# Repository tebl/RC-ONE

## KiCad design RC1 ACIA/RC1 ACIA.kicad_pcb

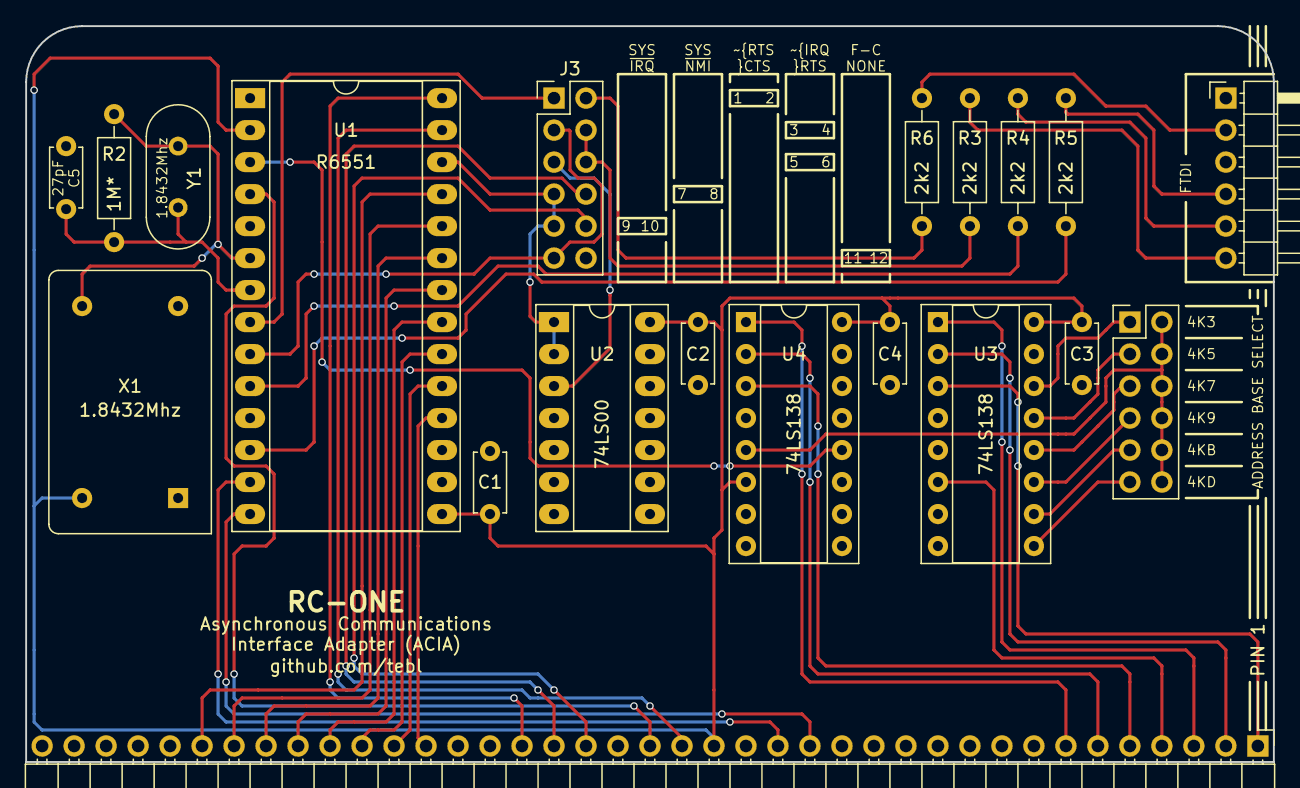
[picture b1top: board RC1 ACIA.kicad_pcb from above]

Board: 2 copper layers, 99.1 x 58.4 mm, 20 parts (0 on the bottom side), 46 nets.

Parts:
C1, C2, C3, C4: 100nF; C_Disc_D4.7mm_W2.5mm_P5.00mm
C5: 27pF; C_Disc_D4.7mm_W2.5mm_P5.00mm
J1: Expansion; Pin_Header_Angled_1x39_Pitch2.54mm
J2: ADDRESS; Pin_Header_Straight_2x06_Pitch2.54mm
J3: CONFIG; Pin_Header_Straight_2x06_Pitch2.54mm
J4: FTDI; Pin_Header_Angled_1x06_Pitch2.54mm
R2: 1M*; R_Axial_DIN0207_L6.3mm_D2.5mm_P10.16mm_Horizontal
R3, R4, R5, R6: 2k2; R_Axial_DIN0207_L6.3mm_D2.5mm_P10.16mm_Horizontal
U1: R6551; DIP-28_W15.24mm_Socket_LongPads
U2: 74LS00; DIP-14_W7.62mm_Socket_LongPads
U3, U4: 74LS138; DIP-16_W7.62mm_Socket
X1: 1.8432Mhz; Oscillator_DIP-14
Y1: 1.8432Mhz; Crystal_HC49-4H_Vertical

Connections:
/4K3: J2.1, U3.14
/4K5: J2.3, U3.13
/4K7: J2.5, U3.12
/4K9: J2.7, U3.11
/4KB: J2.9, U3.10
/4KD: J2.11, U3.9
/A0: J1.16, U1.13
/A1: J1.15, U1.14
/A9: J1.7, U4.1
/A10: J1.6, U4.2
/A11: J1.5, U4.3
/A12: J1.4, U3.6
/A13: J1.3, U3.1
/A14: J1.2, U3.2
/A15: J1.1, U3.3
/D0: J1.27, U1.18
/D1: J1.28, U1.19
/D2: J1.29, U1.20
/D3: J1.30, U1.21
/D4: J1.31, U1.22
/D5: J1.32, U1.23
/D6: J1.33, U1.24
/D7: J1.34, U1.25
/PHI2: J1.19, U1.27
/R/~W: J1.24, U1.28
/RxD: R5.1, U1.12
/TxD: R4.1, U1.10
/~IRQ: J1.22, J3.10
/~NMI: J1.23, J3.8
/~RESET: J1.20, U1.4
GND: C1.2, C2.2, C3.2, C4.2, C5.1, J1.17, J3.12, J4.1, U1.1, U1.16, U1.17, U2.4, U2.5, U2.7, U2.9, U2.10, U2.12, U2.13, U3.4, U3.5, U3.8, U4.4, U4.8, X1.7
unnamed: C5.2, R2.2, U1.7, Y1.2
unnamed: J2.2, J2.4, J2.6, J2.8, J2.10, J2.12, U4.5
unnamed: J3.1, U1.8
unnamed: J3.2, R6.1
unnamed: J3.4, J3.6, R3.1
unnamed: J3.5, U2.3
unnamed: J3.7, J3.9, U1.26, U2.1, U2.2
unnamed: J3.3, J3.11, U1.9
unnamed: J4.2, R6.2
unnamed: J4.4, R5.2
unnamed: J4.5, R4.2
unnamed: J4.6, R3.2
unnamed: R2.1, U1.6, X1.8, Y1.1
VCC: C1.1, C2.1, C3.1, C4.1, J1.18, U1.2, U1.15, U2.14, U3.16, U4.6, U4.16, X1.14
~CS_ACIA: U1.3, U4.12

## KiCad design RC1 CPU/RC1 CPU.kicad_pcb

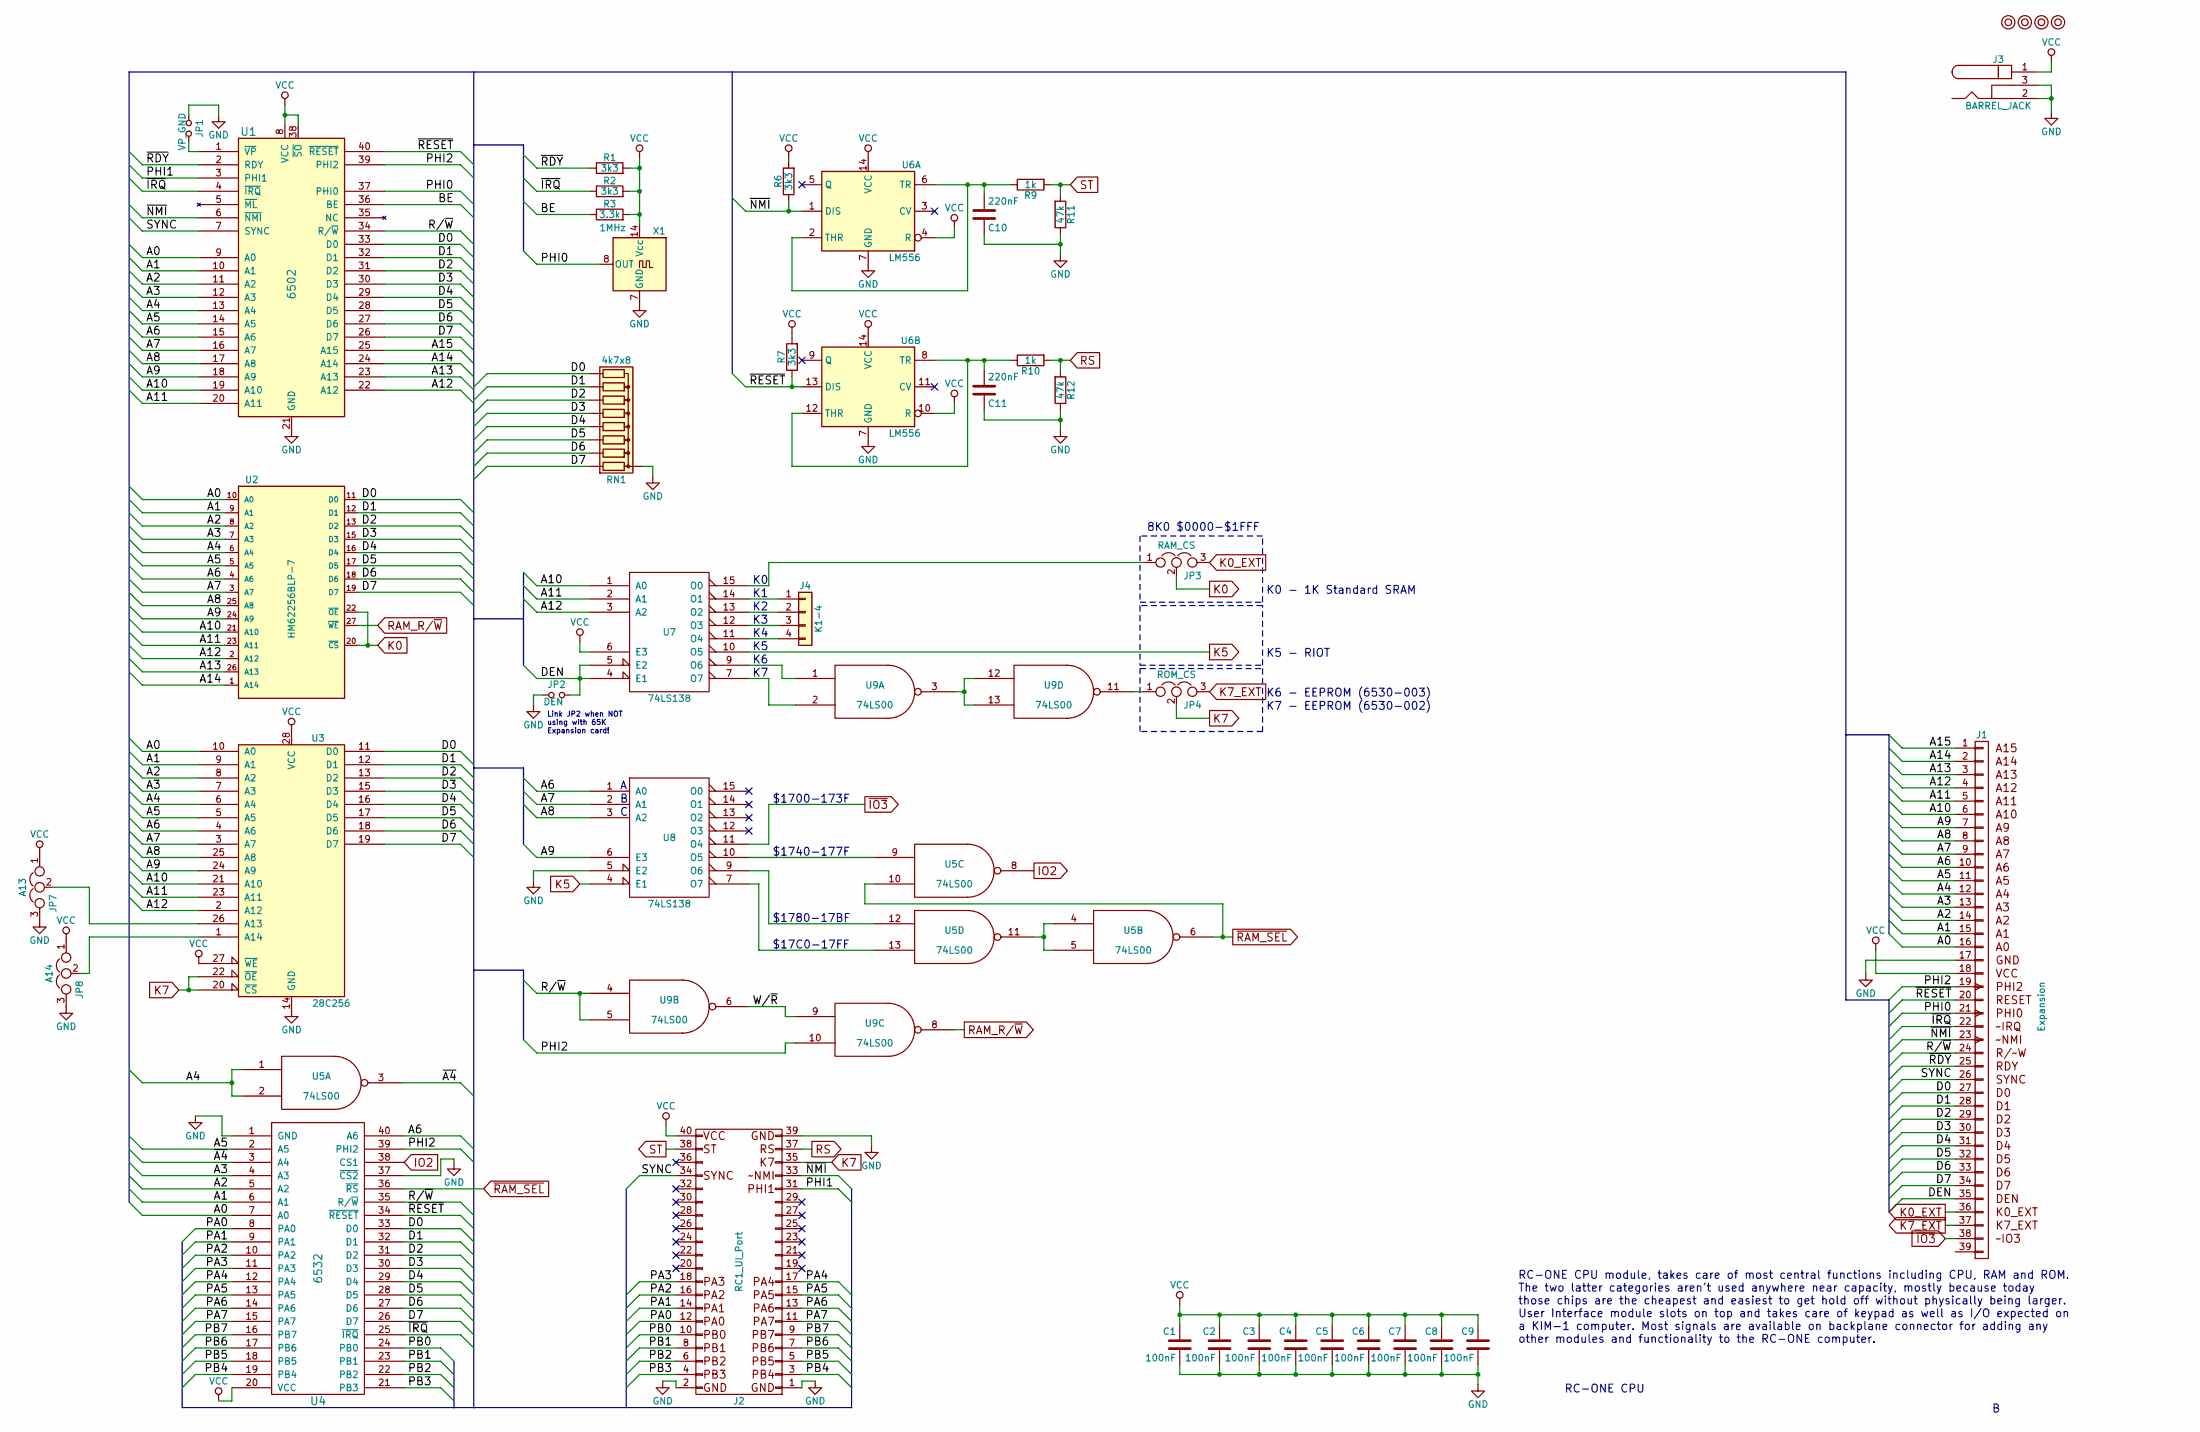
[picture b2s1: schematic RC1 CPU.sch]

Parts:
C1, C2, C3, C4, C5, C6, C7, C8, C9: 100nF; C_Disc_D4.7mm_W2.5mm_P5.00mm
C10, C11: 220nF; C_Disc_D4.7mm_W2.5mm_P5.00mm
J1: Expansion; Pin_Header_Angled_1x39_Pitch2.54mm
J2: RC1_UI_Port; Pin_Header_Straight_2x20_Pitch2.54mm
J3: BARREL_JACK
J4: K1-4; Pin_Header_Straight_1x04_Pitch2.54mm
JP1: VP_GND; Pin_Header_Straight_1x02_Pitch2.54mm
JP2: DEN; Pin_Header_Straight_1x02_Pitch2.54mm
JP3: RAM_CS; Pin_Header_Straight_1x03_Pitch2.54mm
JP4: ROM_CS; Pin_Header_Straight_1x03_Pitch2.54mm
JP7: A13; Pin_Header_Straight_1x03_Pitch2.54mm
JP8: A14; Pin_Header_Straight_1x03_Pitch2.54mm
M1, M2, M3, M4: Mounting; 1pin
R1, R2, R6, R7: 3k3; R_Axial_DIN0207_L6.3mm_D2.5mm_P10.16mm_Horizontal
R3: 3.3k; R_Axial_DIN0207_L6.3mm_D2.5mm_P10.16mm_Horizontal
R9, R10: 1k; R_Axial_DIN0207_L6.3mm_D2.5mm_P10.16mm_Horizontal
R11, R12: 47k; R_Axial_DIN0207_L6.3mm_D2.5mm_P10.16mm_Horizontal
RN1: 4k7x8; R_Array_SIP9
U1: 6502; DIP-40_W15.24mm_Socket
U2: HM62256BLP-7; DIP-28_W15.24mm_Socket
U3: 28C256; DIP-28_W15.24mm_Socket
U4: 6532; DIP-40_W15.24mm_Socket
U5, U9: 74LS00; DIP-14_W7.62mm_Socket
U6: LM556; DIP-14_W7.62mm_Socket
U7, U8: 74LS138; DIP-16_W7.62mm_Socket
X1: 1MHz; Oscillator_DIP-14

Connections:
/A0: J1.16 (A0), U1.9 (A0), U2.10 (A0), U3.10 (A0), U4.7 (A0)
/A1: J1.15 (A1), U1.10 (A1), U2.9 (A1), U3.9 (A1), U4.6 (A1)
/A2: J1.14 (A2), U1.11 (A2), U2.8 (A2), U3.8 (A2), U4.5 (A2)
/A3: J1.13 (A3), U1.12 (A3), U2.7 (A3), U3.7 (A3), U4.4 (A3)
/A4: J1.12 (A4), U1.13 (A4), U2.6 (A4), U3.6 (A4), U5.1, U5.2
/A5: J1.11 (A5), U1.14 (A5), U2.5 (A5), U3.5 (A5), U4.2 (A5)
/A6: J1.10 (A6), U1.15 (A6), U2.4 (A6), U3.4 (A6), U4.40 (A6), U8.1 (A0)
/A7: J1.9 (A7), U1.16 (A7), U2.3 (A7), U3.3 (A7), U8.2 (A1)
/A8: J1.8 (A8), U1.17 (A8), U2.25 (A8), U3.25 (A8), U8.3 (A2)
/A9: J1.7 (A9), U1.18 (A9), U2.24 (A9), U3.24 (A9), U8.6 (E3)
/A10: J1.6 (A10), U1.19 (A10), U2.21 (A10), U3.21 (A10), U7.1 (A0)
/A11: J1.5 (A11), U1.20 (A11), U2.23 (A11), U3.23 (A11), U7.2 (A1)
/A12: J1.4 (A12), U1.22 (A12), U2.2 (A12), U3.2 (A12), U7.3 (A2)
/A13: J1.3 (A13), U1.23 (A13), U2.26 (A13)
/A14: J1.2 (A14), U1.24 (A14), U2.1 (A14)
/A15: J1.1 (A15), U1.25 (A15)
/BE: R3.1, U1.36 (BE)
/D0: J1.27 (D0), RN1.9 (R8), U1.33 (D0), U2.11 (D0), U3.11 (D0), U4.33 (D0)
/D1: J1.28 (D1), RN1.8 (R7), U1.32 (D1), U2.12 (D1), U3.12 (D1), U4.32 (D1)
/D2: J1.29 (D2), RN1.7 (R6), U1.31 (D2), U2.13 (D2), U3.13 (D2), U4.31 (D2)
/D3: J1.30 (D3), RN1.6 (R5), U1.30 (D3), U2.15 (D3), U3.15 (D3), U4.30 (D3)
/D4: J1.31 (D4), RN1.5 (R4), U1.29 (D4), U2.16 (D4), U3.16 (D4), U4.29 (D4)
/D5: J1.32 (D5), RN1.4 (R3), U1.28 (D5), U2.17 (D5), U3.17 (D5), U4.28 (D5)
/D6: J1.33 (D6), RN1.3 (R2), U1.27 (D6), U2.18 (D6), U3.18 (D6), U4.27 (D6)
/D7: J1.34 (D7), RN1.2 (R1), U1.26 (D7), U2.19 (D7), U3.19 (D7), U4.26 (D7)
/DEN: J1.35 (TX), JP2.2, U7.4 (E1), U7.5 (E2)
/PA0: J2.12, U4.8 (PA0)
/PA1: J2.14, U4.9 (PA1)
/PA2: J2.16, U4.10 (PA2)
/PA3: J2.18, U4.11 (PA3)
/PA4: J2.17, U4.12 (PA4)
/PA5: J2.15, U4.13 (PA5)
/PA6: J2.13, U4.14 (PA6)
/PA7: J2.11, U4.15 (PA7)
/PB0: J2.10, U4.24 (PB0)
/PB1: J2.8, U4.23 (PB1)
/PB2: J2.6, U4.22 (PB2)
/PB3: J2.4, U4.21 (PB3)
/PB4: J2.3, U4.19 (PB4)
/PB5: J2.5, U4.18 (PB5)
/PB6: J2.7, U4.17 (PB6)
/PB7: J2.9, U4.16 (PB7)
/PHI0: J1.21 (PHI0), U1.37 (PHI0), X1.8 (OUT)
/PHI1: J2.31, U1.3 (PHI1)
/PHI2: J1.19 (PHI2), U1.39 (PHI2), U4.39 (PHI2), U9.10
/R/~W: J1.24 (RW), U1.34 (R/~W), U4.35 (R/~W), U9.4, U9.5
/SYNC: J1.26 (SYNC), J2.34, U1.7 (SYNC)
/W/~R: U9.6, U9.9
/~A4: U4.3 (A4), U5.3
/~IRQ: J1.22 (IRQ), R2.1, U1.4 (~IRQ), U4.25 (~IRQ)
/~NMI: J1.23 (PHI1), J2.33, R6.1, U1.6 (~NMI), U6.1 (DIS)
/~RDY: J1.25 (READY), R1.1, U1.2 (RDY)
/~RESET: J1.20 (RESET), R7.1, U1.40 (~RESET), U4.34 (~RESET), U6.13 (DIS)
GND: C1.2, C2.2, C3.2, C4.2, C5.2, C6.2, C7.2, C8.2, C9.2, C10.1, C11.1, J1.17, J2.1, J2.2, J2.39, J3.2, J3.3, JP1.2, JP2.1, JP7.3, JP8.3, R11.1, R12.1, RN1.1 (common), U1.21 (GND), U2.14 (GND), U3.14 (GND), U4.1 (GND), U4.37 (~CS2), U5.7 (GND), U6.7 (GND), U7.8 (GND), U8.5 (E2), U8.8 (GND), U9.7 (GND), X1.7 (GND)
IO2: U4.38 (CS1), U5.8
K0: JP3.2, U2.20 (~CS), U2.22 (~OE)
K0_EXT: J1.36 (RX), JP3.3
K5: U7.10 (O5), U8.4 (E1)
K7: J2.35, JP4.2, U3.20 (~CS), U3.22 (~OE)
K7_EXT: J1.37 (NMI), JP4.3
unnamed: C10.2, R9.1, U6.2 (THR), U6.6 (TR)
unnamed: C11.2, R10.1, U6.8 (TR), U6.12 (THR)
unnamed: J4.1, U7.14 (O1)
unnamed: J4.2, U7.13 (O2)
unnamed: J4.3, U7.12 (O3)
unnamed: J4.4, U7.11 (O4)
unnamed: JP1.1, U1.1 (~VP)
unnamed: JP3.1, U7.15 (O0)
unnamed: JP4.1, U9.11
unnamed: JP7.2, U3.26 (A13)
unnamed: JP8.2, U3.1 (A14)
unnamed: U5.9, U8.10 (O5)
unnamed: U5.4, U5.5, U5.11
unnamed: U5.12, U8.9 (O6)
unnamed: U5.13, U8.7 (O7)
unnamed: U7.7 (O7), U9.2
unnamed: U7.9 (O6), U9.1
unnamed: U9.3, U9.12, U9.13
RAM_R/~W: U2.27 (~WE), U9.8
RS: J2.37, R10.2, R12.2
ST: J2.38, R9.2, R11.2
VCC: C1.1, C2.1, C3.1, C4.1, C5.1, C6.1, C7.1, C8.1, C9.1, J1.18, J2.40, J3.1, JP7.1, JP8.1, R1.2, R2.2, R3.2, R6.2, R7.2, U1.8 (VCC), U1.38 (~SO), U2.28 (VCC), U3.27 (~WE), U3.28 (VCC), U4.20 (VCC), U5.14 (VCC), U6.4 (R), U6.10 (R), U6.14 (VCC), U7.6 (E3), U7.16 (VCC), U8.16 (VCC), U9.14 (VCC), X1.14 (Vcc)
~IO3: J1.38, U8.11 (O4)
~RAM_SEL: U4.36 (~RS), U5.6, U5.10

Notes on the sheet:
RC-ONE CPU
RC-ONE CPU module, takes care of most central functions including CPU, RAM and ROM. The two latter categories aren't used anywhere near capacity, mostly because today those chips are the cheapest and easiest to get hold off without physically being larger. User Interface module slots on top and tak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
K0 - 1K Standard SRAM
$17C0-17FF
$1780-17BF
$1740-177F
$1700-173F
K5 - RIOT
K7 - EEPROM (6530-002)
K6 - EEPROM (6530-003)
8K0 $0000-$1FFF
Link JP2 when NOT using with 65K Expansion card!

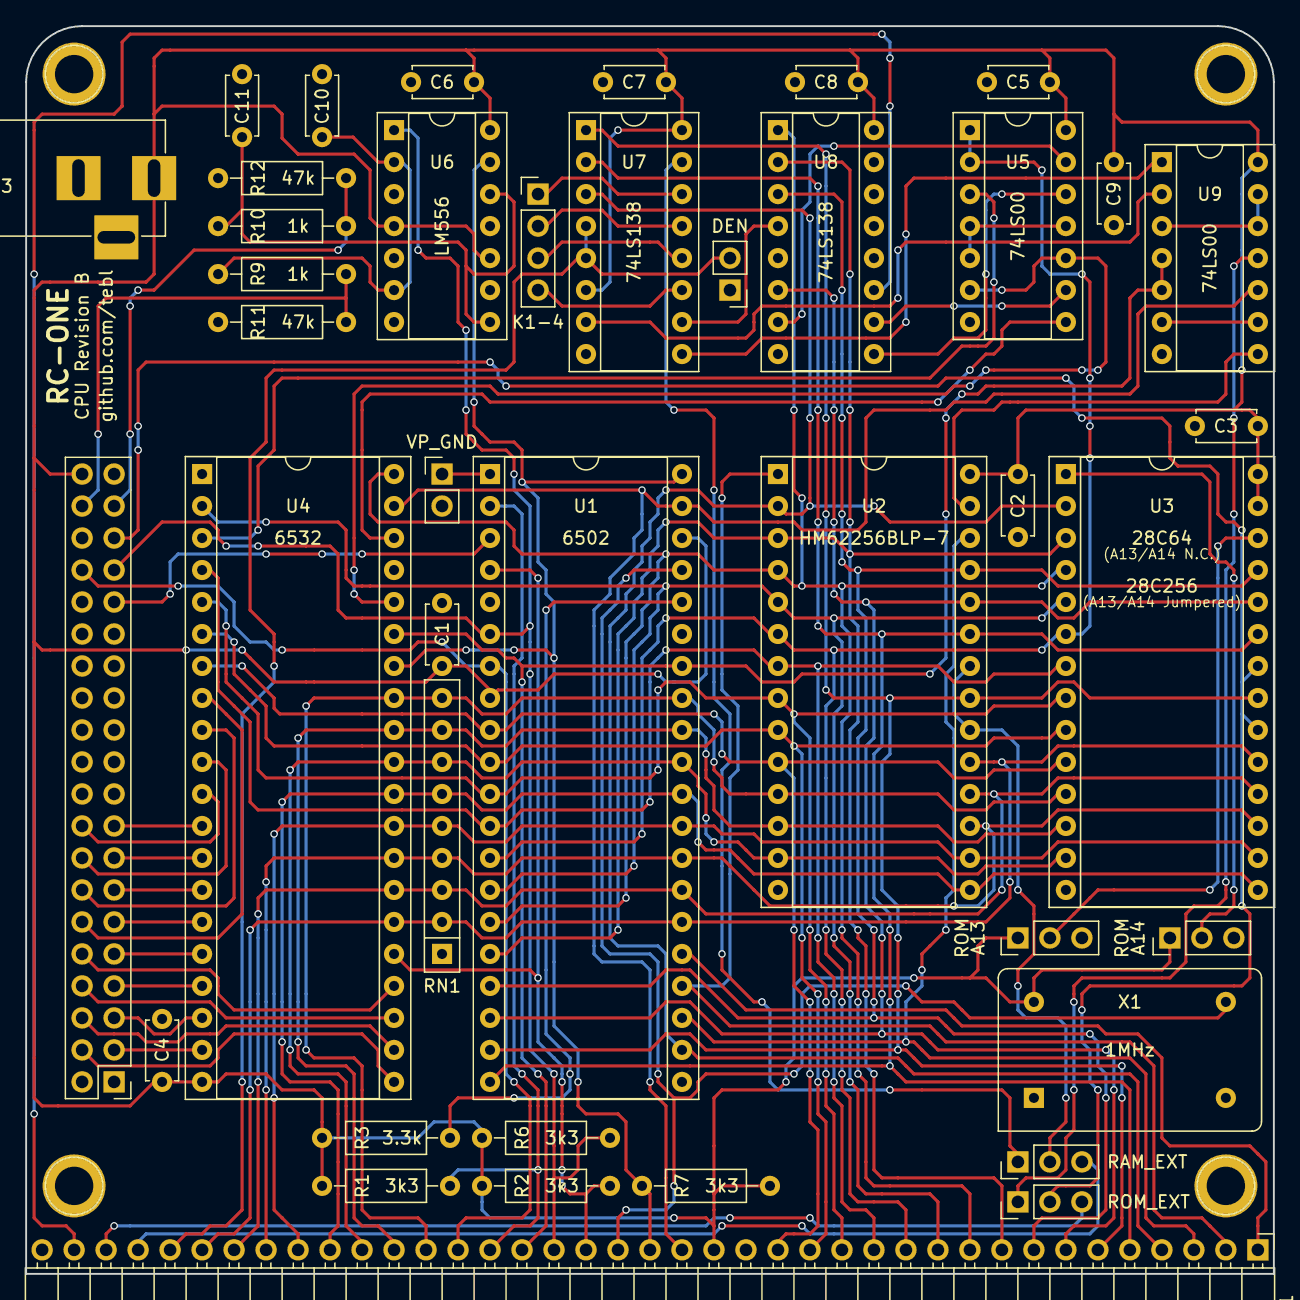
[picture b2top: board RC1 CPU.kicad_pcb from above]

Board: 2 copper layers, 99.1 x 99.1 mm, 45 parts (0 on the bottom side), 84 nets.

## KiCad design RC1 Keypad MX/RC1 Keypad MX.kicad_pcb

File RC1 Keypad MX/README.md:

# RC-ONE

Among the years I've built quite a few computers, some bought as kits from various vendors and some I even designed myself based on available designs describes in books and other technical resources - above all, there was one I really wanted above all of them; the KIM-1! The [RC-ONE](https://github.com/tebl/RC-ONE) is a functional replica designed in a modular fashion, for the specifics see the specific module.

## Keypad MX
The RC-ONE has a keypad with the same key layout as the one found on the original KIM-1 computer, it has been designed so that it can be connected to the computer using a cheap 2x8 pin JTAG cable.

This is the MX version of the keypad, it uses Cherry MX key switches as well as suitable keycaps for that ultimate RC-ONE experience. I built mine using cheaper Gateron clone switches, they're really comfortable for the price and when using the green ones you also get that traditional clicky sound. I was out of white on clear tape for my label printer so 0-F was blank when I took the picture, but overall it's a good look! Add some bumpon rubber feet to the bottom to save the desk from the sharp solder points on the underside.

The Keypad MX might be part of the ultimate RC-ONE experience, but it is a rather expensive build due to the PCB size and components used - the standard [Keypad](https://github.com/tebl/RC-ONE/tree/master/RC1%20Keypad) uses ordinary tactile switches and is a lot cheaper to build. On the other hand, both of these can be connected to your main computer as a USB keyboard by adding the [Keypad USB Adapter](https://github.com/tebl/RC-ONE/tree/master/RC1%20Keypad%20to%20USB) along with an Arduino Pro Micro.

# Schematic
The supplied KiCad files should be sufficient as both a schematic and as a starting point for ordering PCBs (basically you could just zip the contents of the export folder and upload that on a fabrication site), the schematic is also available in [PDF-format](https://github.com/tebl/RC-ONE/raw/master/RC1%20Keypad%20MX/export/RC1%20Keypad%20MX.pdf) so that you print it out and hang it on your office wall, excellent conversation starter at any technology-oriented business worth working at (or so I keep telling myself)!

# BOM
This is the part list as it stands now, most should be easy to get a hold of from your local electronic component shop though you might have to consider other sources depending on the quality of your local vendor.

| Reference          | Item                                     | Count |
| ------------------ | ---------------------------------------- | ----- |
| PCB                | Fabricate yourself using Gerber files    |     1 |
| D1                 | 5mm LED                                  |     1 |
| J1                 | 2x8 straight pin header                  |     1 |
| SW1-SW22,SW23,SW24 | 3 or 5 pin Cherry MX key switches *      |    23 |
| SST                | 1-position DIP switch                    |     1 |
| Keycaps            | Blank 1U keycaps **                      |    23 |
| Keypad cable       | 2x8 pin JTAG cable                       |     1 |

*) Any type of Cherry MX compatible switches can be used, these can be either of the 3 or pin variety. Personally I bought the green Gateron MX switches and they work great though you'd probably want to buy the non-green version if you don't like the clicky sound.

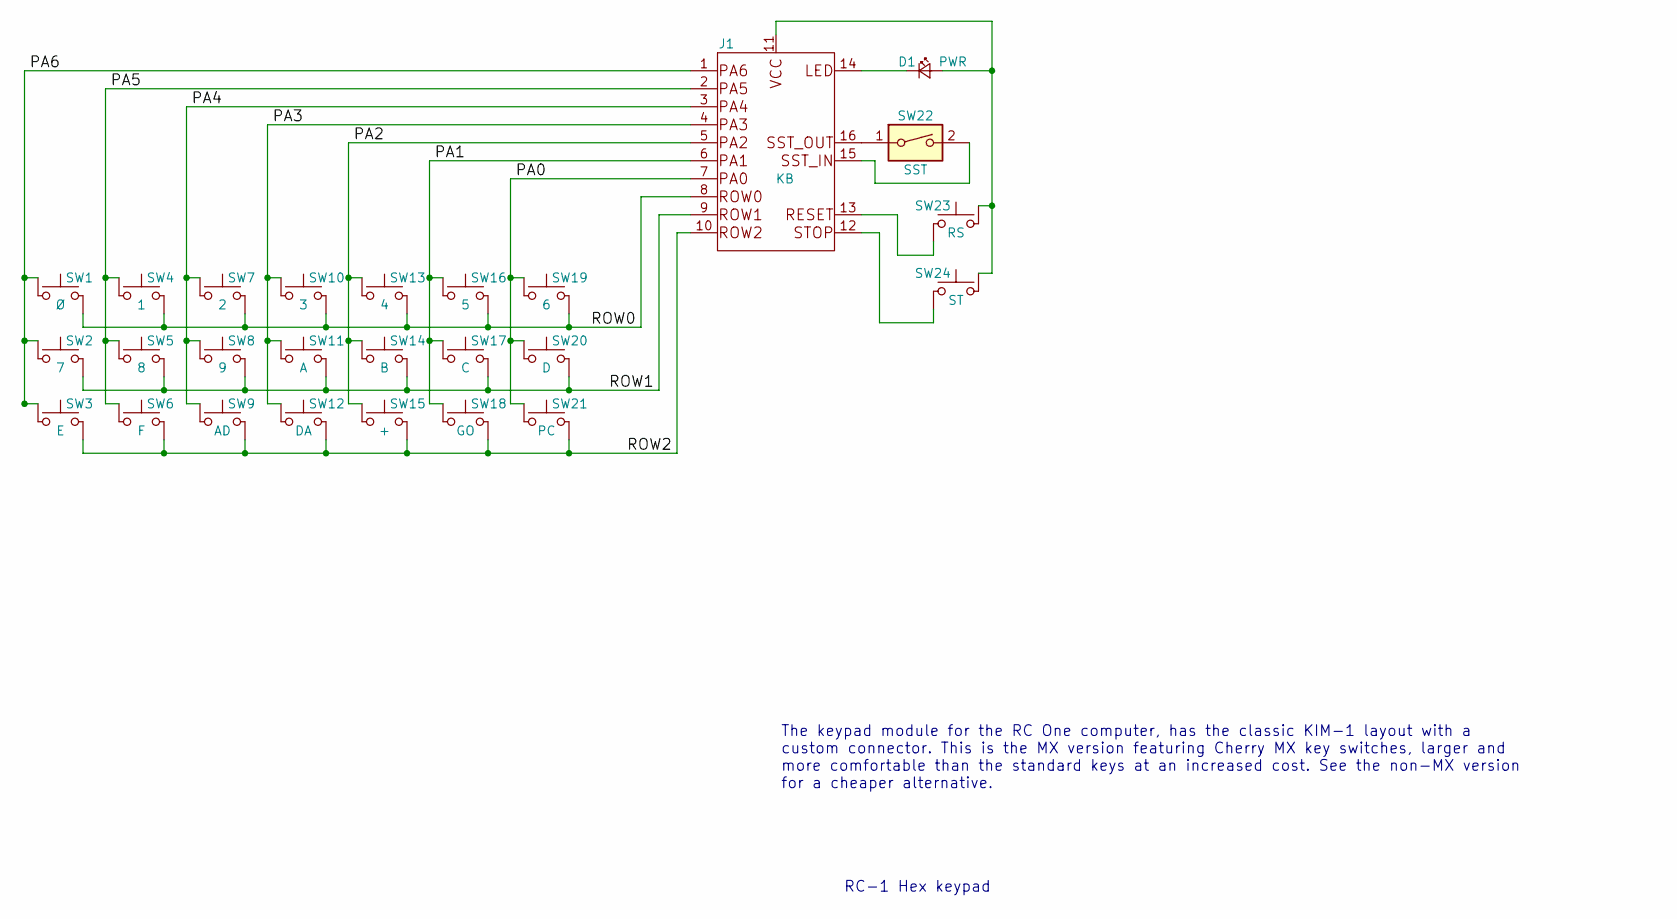
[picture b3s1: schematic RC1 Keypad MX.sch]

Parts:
D1: PWR; LED_D5.0mm
J1: KB; Pin_Header_Straight_2x08_Pitch2.54mm
SW1: Ø; SW_Cherry_MX_1.00u_PCB
SW2: 7; SW_Cherry_MX_1.00u_PCB
SW3: E; SW_Cherry_MX_1.00u_PCB
SW4: 1; SW_Cherry_MX_1.00u_PCB
SW5: 8; SW_Cherry_MX_1.00u_PCB
SW6: F; SW_Cherry_MX_1.00u_PCB
SW7: 2; SW_Cherry_MX_1.00u_PCB
SW8: 9; SW_Cherry_MX_1.00u_PCB
SW9: AD; SW_Cherry_MX_1.00u_PCB
SW10: 3; SW_Cherry_MX_1.00u_PCB
SW11: A; SW_Cherry_MX_1.00u_PCB
SW12: DA; SW_Cherry_MX_1.00u_PCB
SW13: 4; SW_Cherry_MX_1.00u_PCB
SW14: B; SW_Cherry_MX_1.00u_PCB
SW15: +; SW_Cherry_MX_1.00u_PCB
SW16: 5; SW_Cherry_MX_1.00u_PCB
SW17: C; SW_Cherry_MX_1.00u_PCB
SW18: GO; SW_Cherry_MX_1.00u_PCB
SW19: 6; SW_Cherry_MX_1.00u_PCB
SW20: D; SW_Cherry_MX_1.00u_PCB
SW21: PC; SW_Cherry_MX_1.00u_PCB
SW22: SST; SW_DIP_x1_W7.62mm_Slide
SW23: RS; SW_Cherry_MX_1.00u_PCB
SW24: ST; SW_Cherry_MX_1.00u_PCB

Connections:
/PA0: J1.7, SW19.1, SW20.1, SW21.1
/PA1: J1.6, SW16.1, SW17.1, SW18.1
/PA2: J1.5, SW13.1, SW14.1, SW15.1
/PA3: J1.4, SW10.1, SW11.1, SW12.1
/PA4: J1.3, SW7.1, SW8.1, SW9.1
/PA5: J1.2, SW4.1, SW5.1, SW6.1
/PA6: J1.1, SW1.1, SW2.1, SW3.1
/ROW0: J1.8, SW1.2, SW4.2, SW7.2, SW10.2, SW13.2, SW16.2, SW19.2
/ROW1: J1.9, SW2.2, SW5.2, SW8.2, SW11.2, SW14.2, SW17.2, SW20.2
/ROW2: J1.10, SW3.2, SW6.2, SW9.2, SW12.2, SW15.2, SW18.2, SW21.2
unnamed: D1.1 (K), J1.14
unnamed: D1.2 (A), J1.11, SW23.1, SW24.1
unnamed: J1.12, SW24.2
unnamed: J1.13, SW23.2
unnamed: J1.15, SW22.2
unnamed: J1.16, SW22.1

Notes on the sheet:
RC-1 Hex keypad
The keypad module for the RC One computer, has the classic KIM-1 layout with a custom connector. This is the MX version featuring Cherry MX key switches, larger and more comfortable than the standard keys at an increased cost. See the non-MX version for a cheaper alternative.

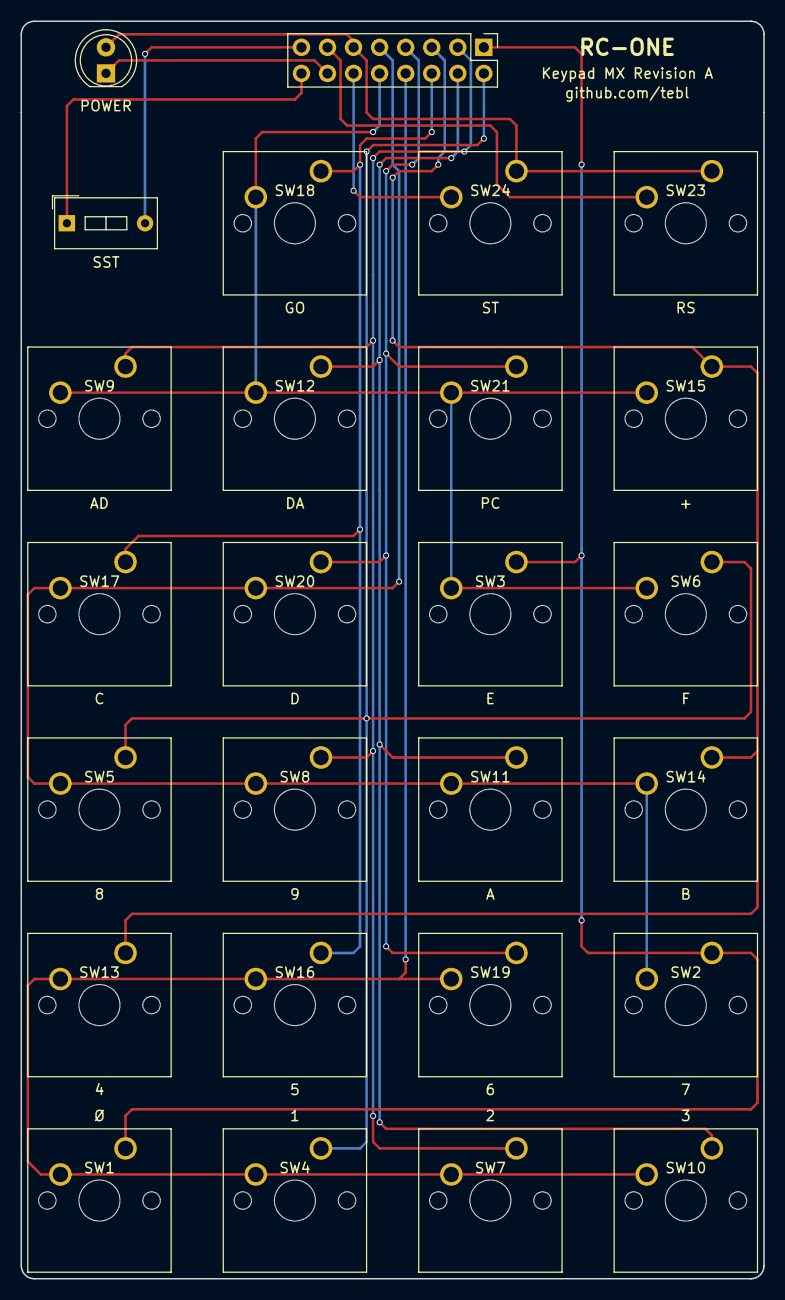
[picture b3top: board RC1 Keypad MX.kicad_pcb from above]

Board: 2 copper layers, 72.4 x 122.6 mm, 26 parts (0 on the bottom side), 16 nets.

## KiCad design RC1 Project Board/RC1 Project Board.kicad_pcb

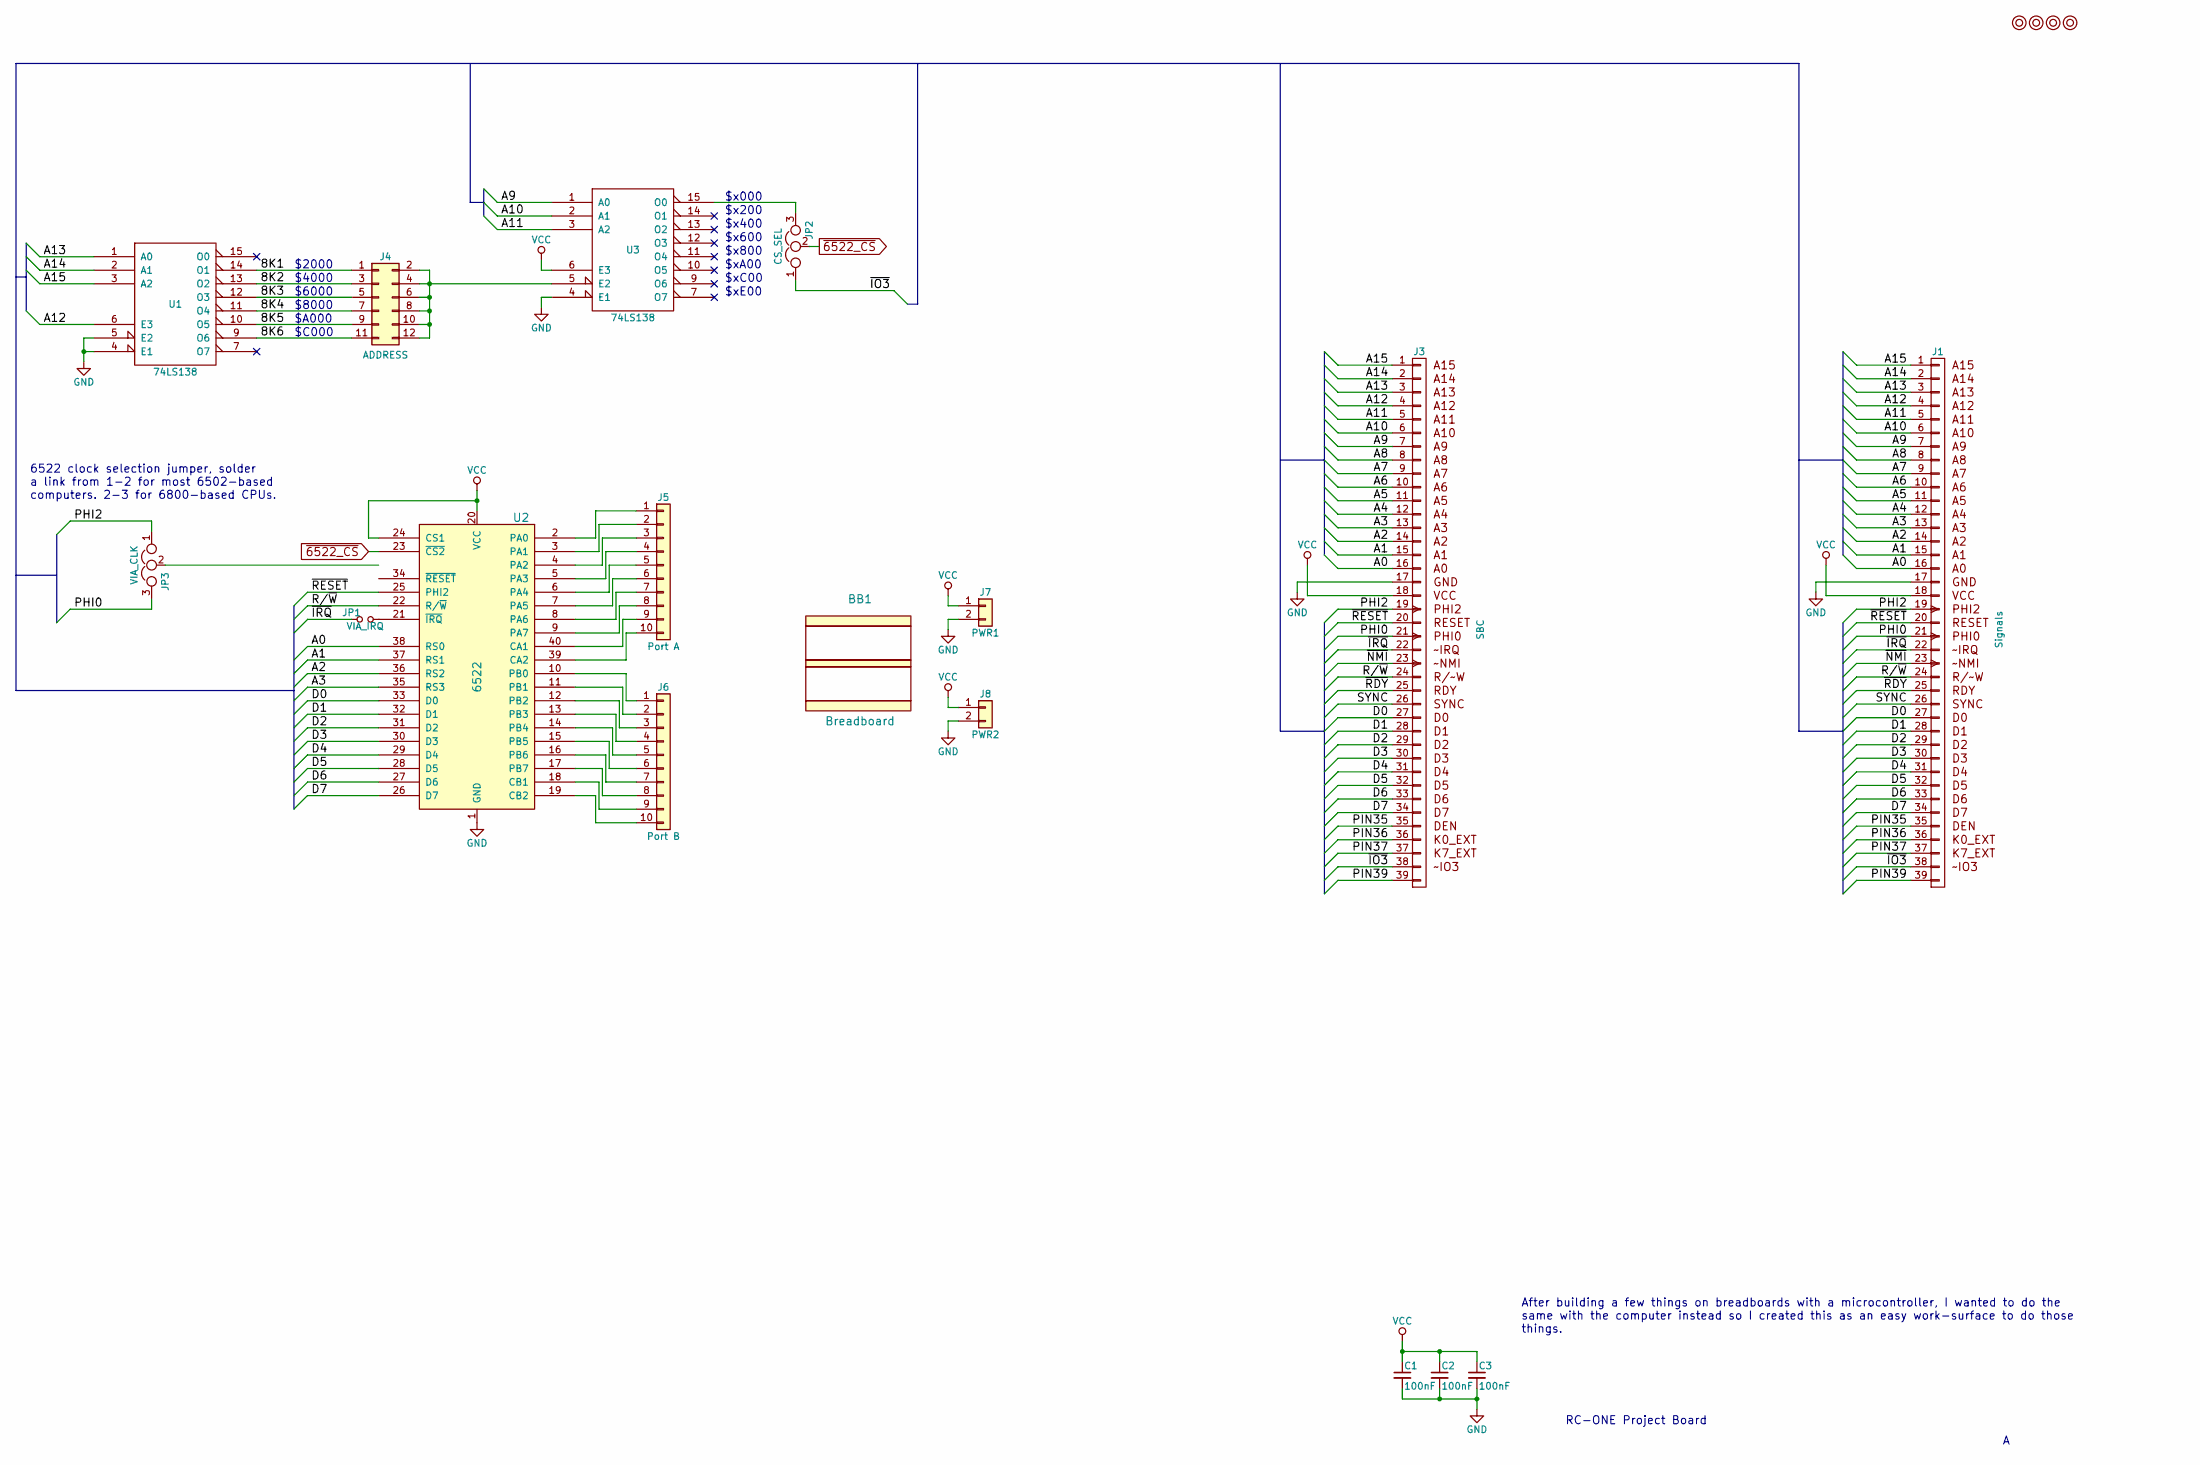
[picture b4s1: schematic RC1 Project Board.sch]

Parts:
BB1: Breadboard; RND 255-00005
C1, C2, C3: 100nF; C_Disc_D4.7mm_W2.5mm_P5.00mm
J1: Signals; Pin_Header_Angled_1x39_Pitch2.54mm
J3: SBC; Pin_Header_Straight_1x39_Pitch2.54mm
J4: ADDRESS; Pin_Header_Straight_2x06_Pitch2.54mm
J5: Port A; Pin_Header_Straight_1x10_Pitch2.54mm
J6: Port B; Pin_Header_Straight_1x10_Pitch2.54mm
J7: PWR1; Pin_Header_Straight_1x02_Pitch2.54mm
J8: PWR2; Pin_Header_Straight_1x02_Pitch2.54mm
JP1: VIA_IRQ; Pin_Header_Straight_1x02_Pitch2.54mm
JP2: CS_SEL; Pin_Header_Straight_1x03_Pitch2.54mm
JP3: VIA_CLK; Pin_Header_Straight_1x03_Pitch2.54mm
M1, M2, M3, M4: Mounting; 1pin
U1, U3: 74LS138; DIP-16_W7.62mm_Socket_LongPads
U2: 6522; DIP-40_W15.24mm_Socket_LongPads

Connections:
/8K1: J4.1, U1.14 (O1)
/8K2: J4.3, U1.13 (O2)
/8K3: J4.5, U1.12 (O3)
/8K4: J4.7, U1.11 (O4)
/8K5: J4.9, U1.10 (O5)
/8K6: J4.11, U1.9 (O6)
/A0: J1.16 (A0), J3.16 (A0), U2.38 (RS0)
/A1: J1.15 (A1), J3.15 (A1), U2.37 (RS1)
/A2: J1.14 (A2), J3.14 (A2), U2.36 (RS2)
/A3: J1.13 (A3), J3.13 (A3), U2.35 (RS3)
/A4: J1.12 (A4), J3.12 (A4)
/A5: J1.11 (A5), J3.11 (A5)
/A6: J1.10 (A6), J3.10 (A6)
/A7: J1.9 (A7), J3.9 (A7)
/A8: J1.8 (A8), J3.8 (A8)
/A9: J1.7 (A9), J3.7 (A9), U3.1 (A0)
/A10: J1.6 (A10), J3.6 (A10), U3.2 (A1)
/A11: J1.5 (A11), J3.5 (A11), U3.3 (A2)
/A12: J1.4 (A12), J3.4 (A12), U1.6 (E3)
/A13: J1.3 (A13), J3.3 (A13), U1.1 (A0)
/A14: J1.2 (A14), J3.2 (A14), U1.2 (A1)
/A15: J1.1 (A15), J3.1 (A15), U1.3 (A2)
/D0: J1.27 (D0), J3.27 (D0), U2.33 (D0)
/D1: J1.28 (D1), J3.28 (D1), U2.32 (D1)
/D2: J1.29 (D2), J3.29 (D2), U2.31 (D2)
/D3: J1.30 (D3), J3.30 (D3), U2.30 (D3)
/D4: J1.31 (D4), J3.31 (D4), U2.29 (D4)
/D5: J1.32 (D5), J3.32 (D5), U2.28 (D5)
/D6: J1.33 (D6), J3.33 (D6), U2.27 (D6)
/D7: J1.34 (D7), J3.34 (D7), U2.26 (D7)
/PHI0: J1.21 (PHI0), J3.21 (PHI0), JP3.3
/PHI2: J1.19 (PHI2), J3.19 (PHI2), JP3.1
/PIN35: J1.35 (TX), J3.35 (TX)
/PIN36: J1.36 (RX), J3.36 (RX)
/PIN37: J1.37 (NMI), J3.37 (NMI)
/PIN39: J1.39, J3.39
/R/~W: J1.24 (RW), J3.24 (RW), U2.22 (R/~W)
/SYNC: J1.26 (SYNC), J3.26 (SYNC)
/~IO3: J1.38, J3.38, JP2.1
/~IRQ: J1.22 (IRQ), J3.22 (IRQ), JP1.1
/~NMI: J1.23 (PHI1), J3.23 (PHI1)
/~RDY: J1.25 (READY), J3.25 (READY)
GND: C1.2, C2.2, C3.2, J1.17, J3.17, J7.2, J8.2, U1.4 (E1), U1.5 (E2), U1.8 (GND), U2.1 (GND), U3.4 (E1), U3.8 (GND)
unnamed: J4.2, J4.4, J4.6, J4.8, J4.10, J4.12, U3.5 (E2)
unnamed: J5.1, U2.2 (PA0)
unnamed: J5.2, U2.3 (PA1)
unnamed: J5.3, U2.4 (PA2)
unnamed: J5.4, U2.5 (PA3)
unnamed: J5.5, U2.6 (PA4)
unnamed: J5.6, U2.7 (PA5)
unnamed: J5.7, U2.8 (PA6)
unnamed: J5.8, U2.9 (PA7)
unnamed: J5.9, U2.40 (CA1)
unnamed: J5.10, U2.39 (CA2)
unnamed: J6.1, U2.10 (PB0)
unnamed: J6.2, U2.11 (PB1)
unnamed: J6.3, U2.12 (PB2)
unnamed: J6.4, U2.13 (PB3)
unnamed: J6.5, U2.14 (PB4)
unnamed: J6.6, U2.15 (PB5)
unnamed: J6.7, U2.16 (PB6)
unnamed: J6.8, U2.17 (PB7)
unnamed: J6.9, U2.18 (CB1)
unnamed: J6.10, U2.19 (CB2)
unnamed: JP1.2, U2.21 (~IRQ)
unnamed: JP2.3, U3.15 (O0)
VCC: C1.1, C2.1, C3.1, J1.18, J3.18, J7.1, J8.1, U1.16 (VCC), U2.20 (VCC), U2.24 (CS1), U3.6 (E3), U3.16 (VCC)
~6522_CS: JP2.2, U2.23 (~CS2)

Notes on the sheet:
RC-ONE Project Board
After building a few things on breadboards with a microcontroller, I wanted to do the same with the computer instead so I created this as an easy work-surface to do those things.
$2000
$4000
$6000
$8000
$A000
$C000
$x000
$xE00
$x400
$x200
$x600
$x800
$xC00
$xA00
6522 clock selection jumper, solder a link from 1-2 for most 6502-based computers. 2-3 for 6800-based CPUs.

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
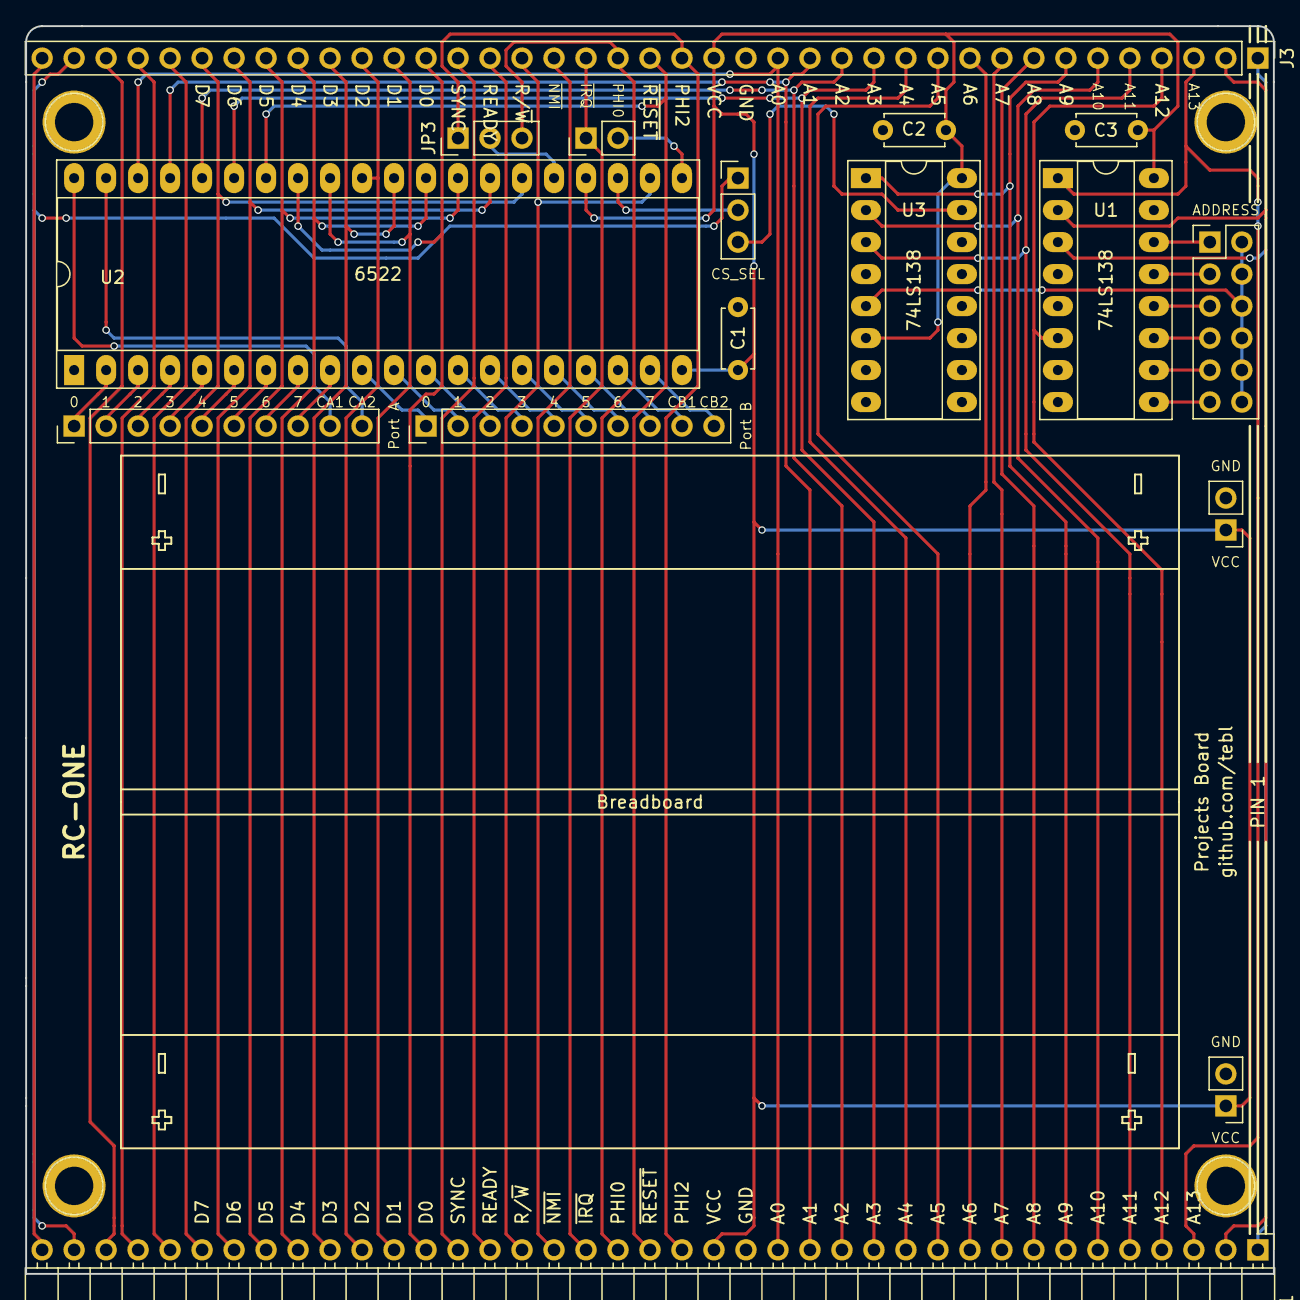
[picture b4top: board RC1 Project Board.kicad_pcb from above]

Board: 2 copper layers, 99.1 x 99.1 mm, 21 parts (0 on the bottom side), 70 nets.
